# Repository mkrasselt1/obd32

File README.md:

# obd32
The goal of this project is to create a esp32 based pcb and software to
catch and submit automotive data from obd2 ports of supported vehicles 
to a given (list of ) endpoints(s). 

Anyone is free to join our goal to make the hardware reliable and affordable.

current plan conatins the featureset of:

    - esp32 based microprocessor
    - direct canbus via tranciever chip MCP2562-e
    - db9 for obd2 connection
    - wifi connection to hotsport or
    - onboard switchable usb port for lte-wifi-router 
    - ~~bluetooth connection compatible with elm327ds~~
    - micro sd card slot for configuration, logging and cache
    - ota updates via github releases
    - build in webfrontend
    - low power sleep mode (canbus activity and battery voltage)
    - gps for location and altitude sync
    - communication protocolls: https-post, websocket, mqtt

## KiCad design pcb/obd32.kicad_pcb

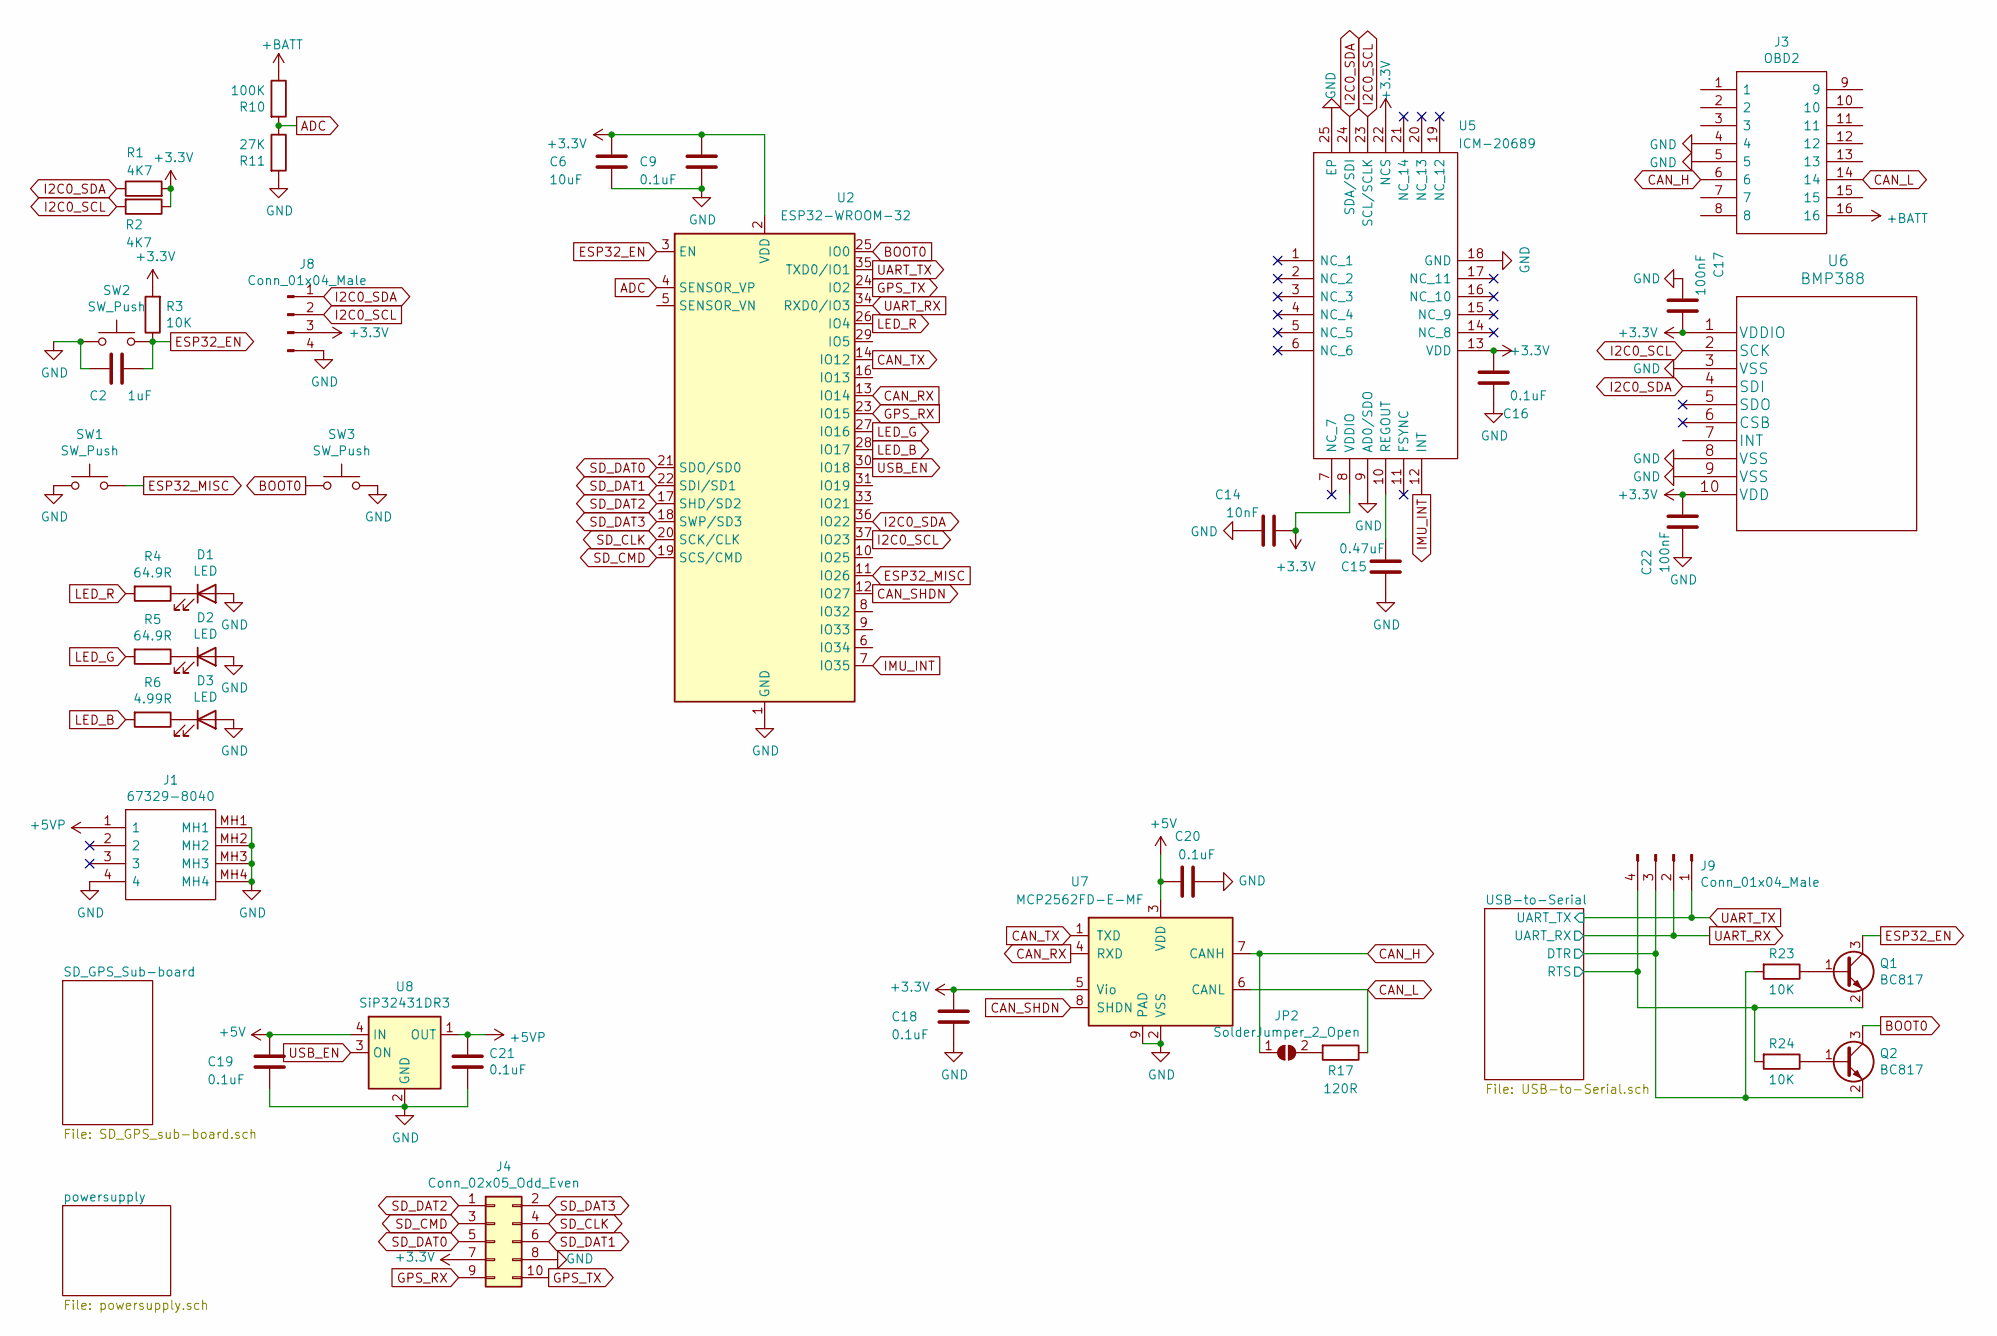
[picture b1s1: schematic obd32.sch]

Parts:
C2: 1uF; C_0402_1005Metric
C6: 10uF; C_0805_2012Metric
C9, C16, C18, C19, C20, C21: 0.1uF; C_0402_1005Metric
C14: 10nF; C_0402_1005Metric
C15: 0.47uF; C_0402_1005Metric
C17, C22: 100nF; C_0402_1005Metric
D1, D2, D3: LED; LED_0402_1005Metric
J1: 67329-8040; 673298040; Manufacturer_Part_Number 67329-8040; Mouser Part Number 538-67329-8040
J3: OBD2; Manufacturer_Part_Number OBD2
J4: Conn_02x05_Odd_Even; PinSocket_2x05_P2.54mm_Vertical
J8, J9: Conn_01x04_Male; PinHeader_1x04_P2.54mm_Vertical
JP2: SolderJumper_2_Open; SolderJumper-2_P1.3mm_Open_RoundedPad1.0x1.5mm
Q1, Q2: BC817; SOT-23
R1, R2: 4K7; R_0603_1608Metric
R3, R23, R24: 10K; R_0402_1005Metric
R4, R5: 64.9R; R_0402_1005Metric
R6: 4.99R; R_0402_1005Metric
R10: 100K; R_0402_1005Metric
R11: 27K; R_0402_1005Metric
R17: 120R; R_0402_1005Metric
SW1, SW2, SW3: SW_Push; SW_SPST_B3U-3000P-B
U2: ESP32-WROOM-32; ESP32-WROOM-32U
U5: ICM-20689; QFN50P400X400X95-25N-D; Manufacturer_Part_Number ICM-20689; Mouser Part Number 410-ICM-20689
U6: BMP388
U7: MCP2562FD-E-MF; DFN-8-1EP_3x3mm_P0.65mm_EP1.55x2.4mm
U8: SiP32431DR3; SOT-363_SC-70-6

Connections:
+3V3: C6.1, C9.1, C14.2, C16.2, C17.2, C18.2, C22.2, J4.7, J8.3, R1.2, R2.1, R3.2, U2.2 (VDD), U5.8 (VDDIO), U5.13 (VDD), U5.22 (NCS), U6.1 (VDDIO), U6.10 (VDD), U7.5 (Vio); also elsewhere on the board
+5V: C19.1, C20.1, U7.3 (VDD), U8.4 (IN); also elsewhere on the board
+5VP: C21.1, J1.1, U8.1 (OUT)
+BATT: J3.16, R10.1; also elsewhere on the board
/USB-to-Serial/DTR: J9.3, Q2.2 (E), R23.2; also elsewhere on the board
/USB-to-Serial/RTS: J9.4, Q1.2 (E), R24.2; also elsewhere on the board
ADC: R10.2, R11.1, U2.4 (SENSOR_VP)
BOOT0: Q2.3 (C), SW3.1, U2.25 (IO0)
CAN_H: J3.6, JP2.1 (A), U7.7 (CANH)
CAN_L: J3.14, R17.1, U7.6 (CANL)
CAN_RX: U2.13 (IO14), U7.4 (RXD)
CAN_SHDN: U2.12 (IO27), U7.8 (SHDN)
CAN_TX: U2.14 (IO12), U7.1 (TXD)
ESP32_EN: C2.2, Q1.3 (C), R3.1, SW2.2, U2.3 (EN)
ESP32_MISC: SW1.2, U2.11 (IO26)
GND: C2.1, C6.2, C9.2, C14.1, C15.1, C16.1, C17.1, C18.1, C19.2, C20.2, C21.2, C22.1, D1.2 (A), D2.2 (A), D3.2 (A), J1.4, J1.MH1, J1.MH2, J1.MH3, J1.MH4, J3.4, J3.5, J4.8, J8.4, R11.2, SW1.1, SW2.1, SW3.2, U2.1 (GND), U2.15 (GND), U2.38 (GND), U2.39 (GND), U5.9 (AD0/SDO), U5.18 (GND), U5.25 (EP), U6.3 (VSS), U6.8 (VSS), U6.9 (VSS), U7.2 (VSS), U7.9 (PAD), U8.2 (GND), U8.5 (GND); also elsewhere on the board
GPS_RX: J4.9, U2.23 (IO15)
GPS_TX: J4.10, U2.24 (IO2)
I2C0_SCL: J8.2, R2.2, U2.37 (IO23), U5.23 (SCL/SCLK), U6.2 (SCK)
I2C0_SDA: J8.1, R1.1, U2.36 (IO22), U5.24 (SDA/SDI), U6.4 (SDI)
IMU_INT: U2.7 (IO35), U5.12 (INT)
LED_B: R6.2, U2.28 (IO17)
LED_G: R5.2, U2.27 (IO16)
LED_R: R4.2, U2.26 (IO4)
unnamed: C15.2, U5.10 (REGOUT)
unnamed: D1.1 (K), R4.1
unnamed: D2.1 (K), R5.1
unnamed: D3.1 (K), R6.1
unnamed: JP2.2 (B), R17.2
unnamed: Q1.1 (B), R23.1
unnamed: Q2.1 (B), R24.1
SD_CLK: J4.4, U2.20 (SCK/CLK)
SD_CMD: J4.3, U2.19 (SCS/CMD)
SD_DAT0: J4.5, U2.21 (SDO/SD0)
SD_DAT1: J4.6, U2.22 (SDI/SD1)
SD_DAT2: J4.1, U2.17 (SHD/SD2)
SD_DAT3: J4.2, U2.18 (SWP/SD3)
UART_RX: J9.2, U2.34 (RXD0/IO3); also elsewhere on the board
UART_TX: J9.1, U2.35 (TXD0/IO1); also elsewhere on the board
USB_EN: U2.30 (IO18), U8.3 (ON)

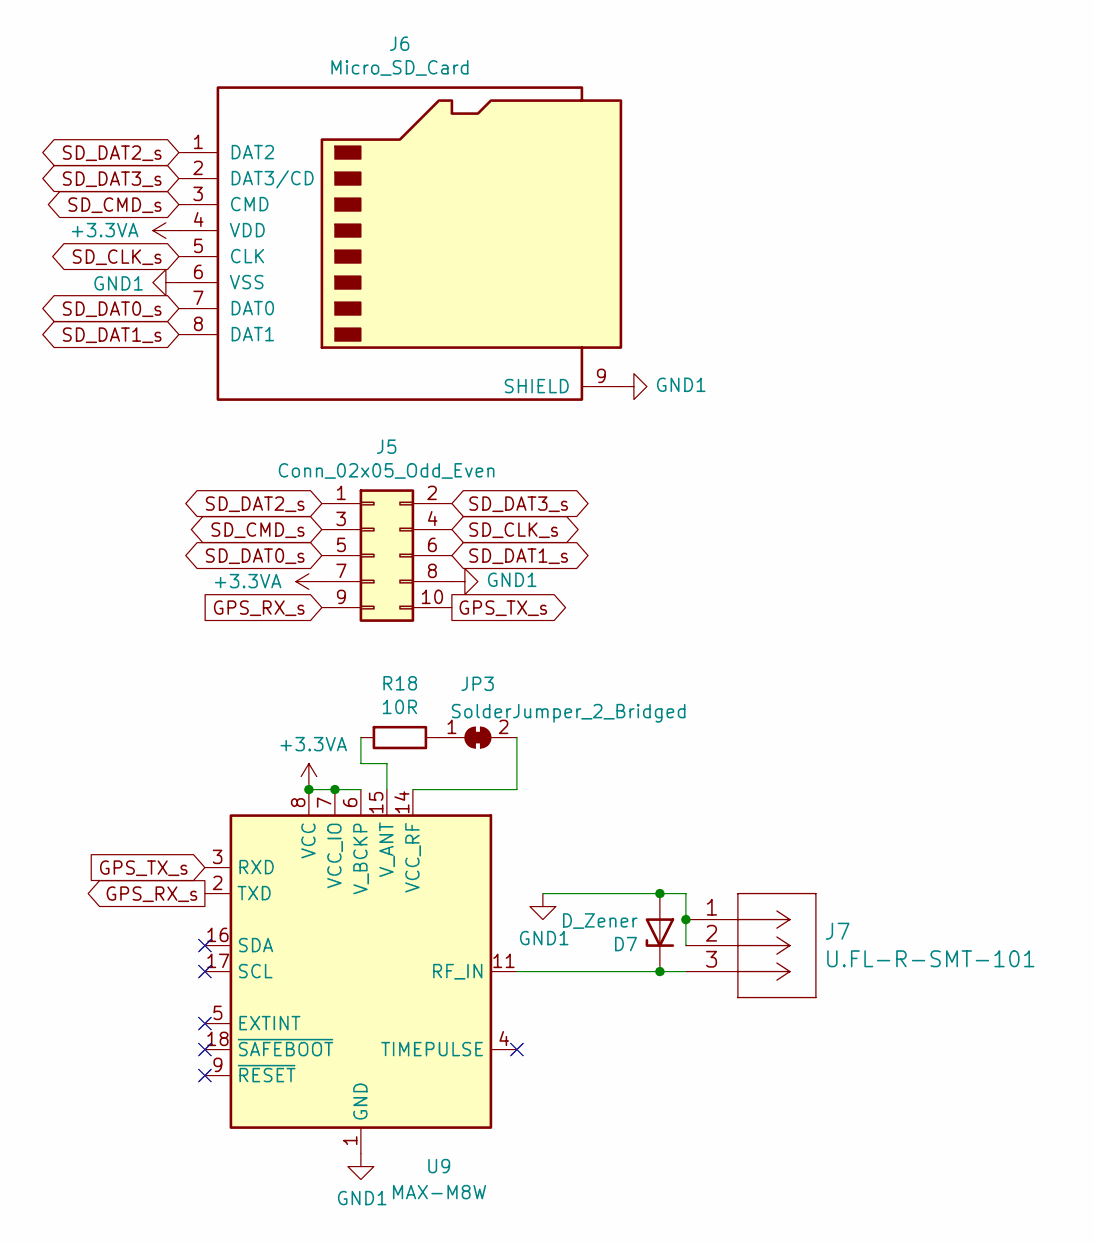
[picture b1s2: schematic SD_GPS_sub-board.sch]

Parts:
D7: D_Zener; D_0201_0603Metric
J5: Conn_02x05_Odd_Even; PinHeader_2x05_P2.54mm_Vertical
J6: Micro_SD_Card; microSD_HC_Hirose_DM3AT-SF-PEJM5
J7: U.FL-R-SMT-101
JP3: SolderJumper_2_Bridged; SolderJumper-2_P1.3mm_Bridged_RoundedPad1.0x1.5mm
R18: 10R; R_0402_1005Metric
U9: MAX-M8W; ublox_MAX

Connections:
+3.3VA: J5.7, J6.4 (VDD), U9.6 (V_BCKP), U9.7 (VCC_IO), U9.8 (VCC)
GND1: D7.2 (A), J5.8, J6.6 (VSS), J6.9 (SHIELD), J7.1 (GND), J7.2 (GND), U9.1 (GND), U9.10 (GND), U9.12 (GND)
GPS_RX_s: J5.9, U9.2 (TXD)
GPS_TX_s: J5.10, U9.3 (RXD)
unnamed: D7.1 (K), J7.3 (SIG), U9.11 (RF_IN)
unnamed: JP3.1 (A), R18.1
unnamed: JP3.2 (B), U9.14 (VCC_RF)
unnamed: R18.2, U9.15 (V_ANT)
SD_CLK_s: J5.4, J6.5 (CLK)
SD_CMD_s: J5.3, J6.3 (CMD)
SD_DAT0_s: J5.5, J6.7 (DAT0)
SD_DAT1_s: J5.6, J6.8 (DAT1)
SD_DAT2_s: J5.1, J6.1 (DAT2)
SD_DAT3_s: J5.2, J6.2 (DAT3/CD)

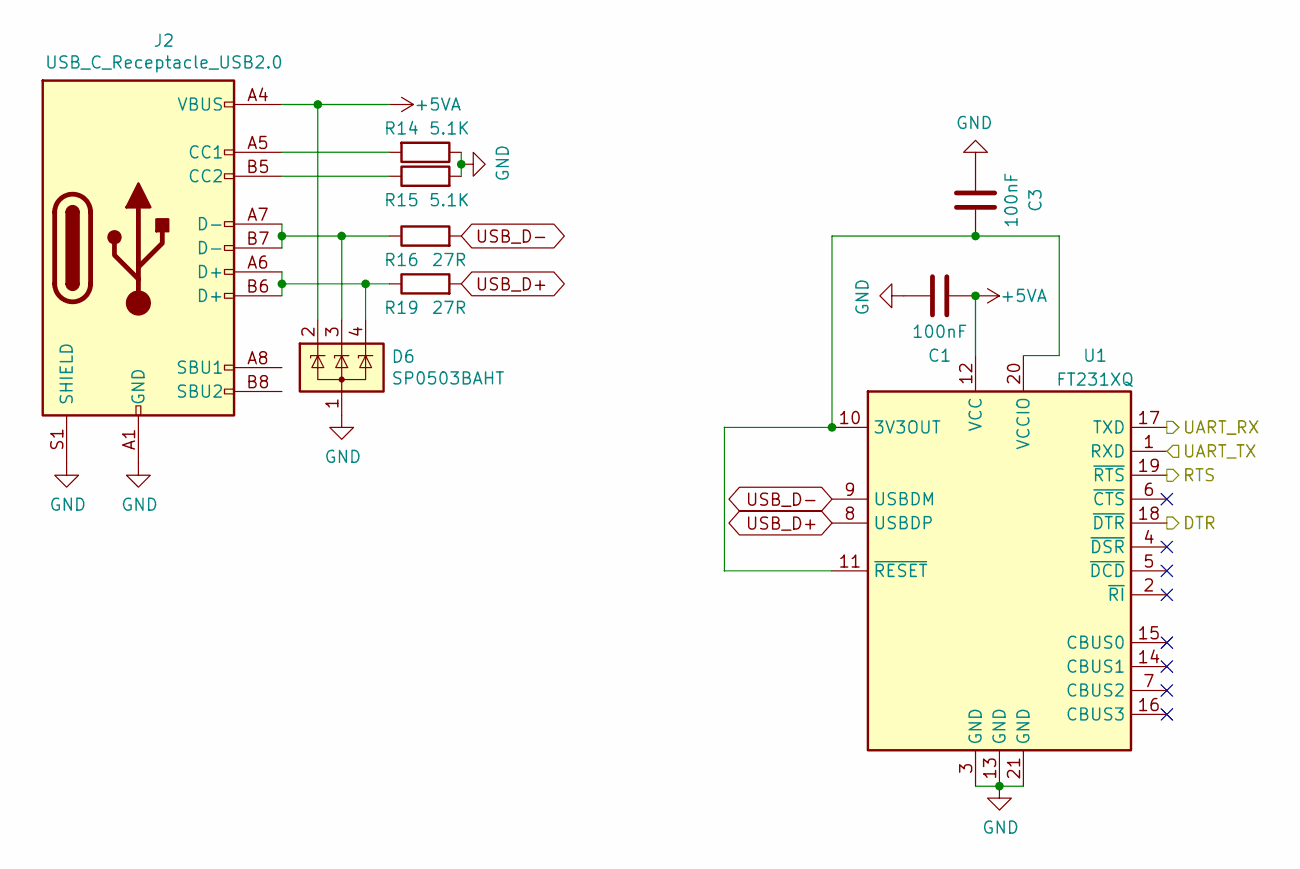
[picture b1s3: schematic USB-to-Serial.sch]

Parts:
C1, C3: 100nF; C_0805_2012Metric
D6: SP0503BAHT; SOT-143
J2: USB_C_Receptacle_USB2.0; USB_C_Receptacle_JAE_DX07S016JA1
R14, R15: 5.1K; R_0402_1005Metric
R16, R19: 27R; R_0402_1005Metric
U1: FT231XQ; QFN-20-1EP_4x4mm_P0.5mm_EP2.5x2.5mm

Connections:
+5VA: C1.2, D6.2 (K), J2.A4 (VBUS), J2.A9 (VBUS), J2.B4 (VBUS), J2.B9 (VBUS), U1.12 (VCC); also elsewhere on the board
/USB-to-Serial/DTR: U1.18 (~DTR); also elsewhere on the board
/USB-to-Serial/RTS: U1.19 (~RTS); also elsewhere on the board
GND: C1.1, C3.2, D6.1 (A), J2.A1 (GND), J2.A12 (GND), J2.B1 (GND), J2.B12 (GND), J2.S1 (SHIELD), R14.1, R15.2, U1.3 (GND), U1.13 (GND), U1.21 (GND); also elsewhere on the board
unnamed: C3.1, U1.10 (3V3OUT), U1.11 (~RESET), U1.20 (VCCIO)
unnamed: D6.3 (K), J2.A7 (D-), J2.B7 (D-), R16.1
unnamed: D6.4 (K), J2.A6 (D+), J2.B6 (D+), R19.1
unnamed: J2.A5 (CC1), R14.2
unnamed: J2.B5 (CC2), R15.1
UART_RX: U1.17 (TXD); also elsewhere on the board
UART_TX: U1.1 (RXD); also elsewhere on the board
USB_D+: R19.2, U1.8 (USBDP)
USB_D-: R16.2, U1.9 (USBDM)

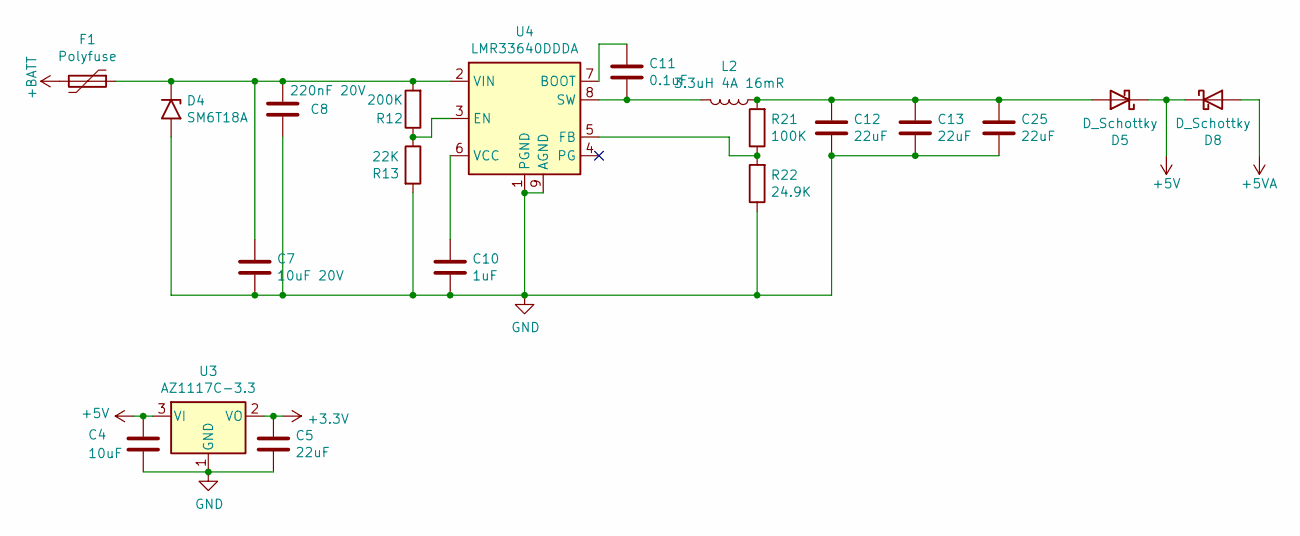
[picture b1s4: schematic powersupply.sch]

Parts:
C4: 10uF; C_0805_2012Metric
C5, C12, C13, C25: 22uF; C_0805_2012Metric
C7: 10uF 20V; C_0805_2012Metric
C8: 220nF 20V; C_0402_1005Metric
C10: 1uF; C_0402_1005Metric
C11: 0.1uF; C_0402_1005Metric
D4: SM6T18A; D_SMB
D5, D8: D_Schottky; D_SMA
F1: Polyfuse; Fuse_1812_4532Metric_Castellated
L2: 3.3uH 4A 16mR; TDK_SPM5030
R12: 200K; R_0402_1005Metric
R13: 22K; R_0402_1005Metric
R21: 100K; R_0402_1005Metric
R22: 24.9K; R_0402_1005Metric
U3: AZ1117C-3.3; SOT-89-3
U4: LMR33640DDDA; Texas_HSOP-8-1EP_3.9x4.9mm_P1.27mm_ThermalVias

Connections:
+3V3: C5.1, U3.2 (VO); also elsewhere on the board
+5V: C4.1, D5.1 (K), D8.1 (K), U3.3 (VI); also elsewhere on the board
+5VA: D8.2 (A); also elsewhere on the board
+BATT: F1.2; also elsewhere on the board
GND: C4.2, C5.2, C7.2, C8.2, C10.2, C12.2, C13.2, C25.2, D4.2 (A2), R13.2, R22.1, U3.1 (GND), U4.1 (PGND), U4.9 (AGND); also elsewhere on the board
unnamed: C7.1, C8.1, D4.1 (A1), F1.1, R12.2, U4.2 (VIN)
unnamed: C10.1, U4.6 (VCC)
unnamed: C11.1, U4.7 (BOOT)
unnamed: C11.2, L2.2, U4.8 (SW)
unnamed: C12.1, C13.1, C25.1, D5.2 (A), L2.1, R21.2
unnamed: R12.1, R13.1, U4.3 (EN)
unnamed: R21.1, R22.2, U4.5 (FB)

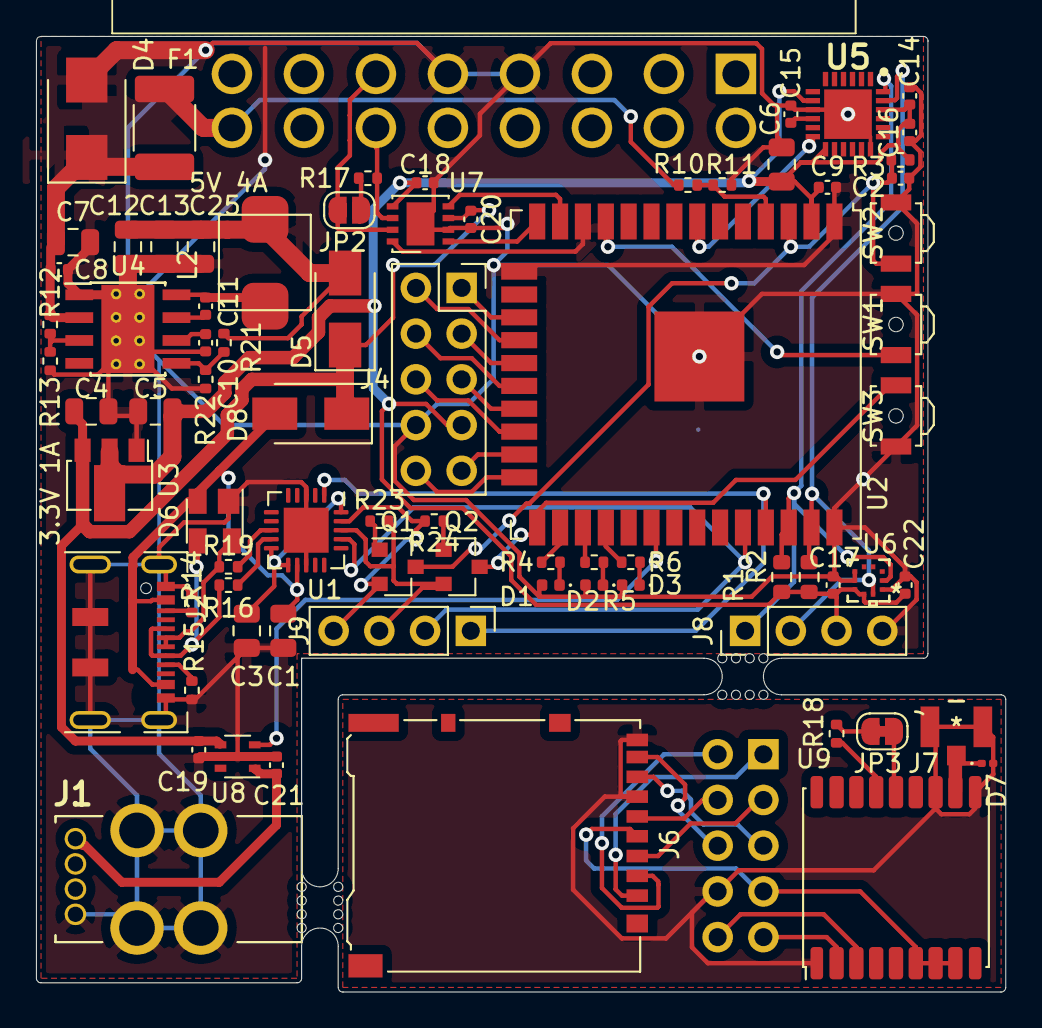
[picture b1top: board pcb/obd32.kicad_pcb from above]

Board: 2 copper layers, 53.8 x 53.1 mm, 78 parts (1 on the bottom side), 69 nets.

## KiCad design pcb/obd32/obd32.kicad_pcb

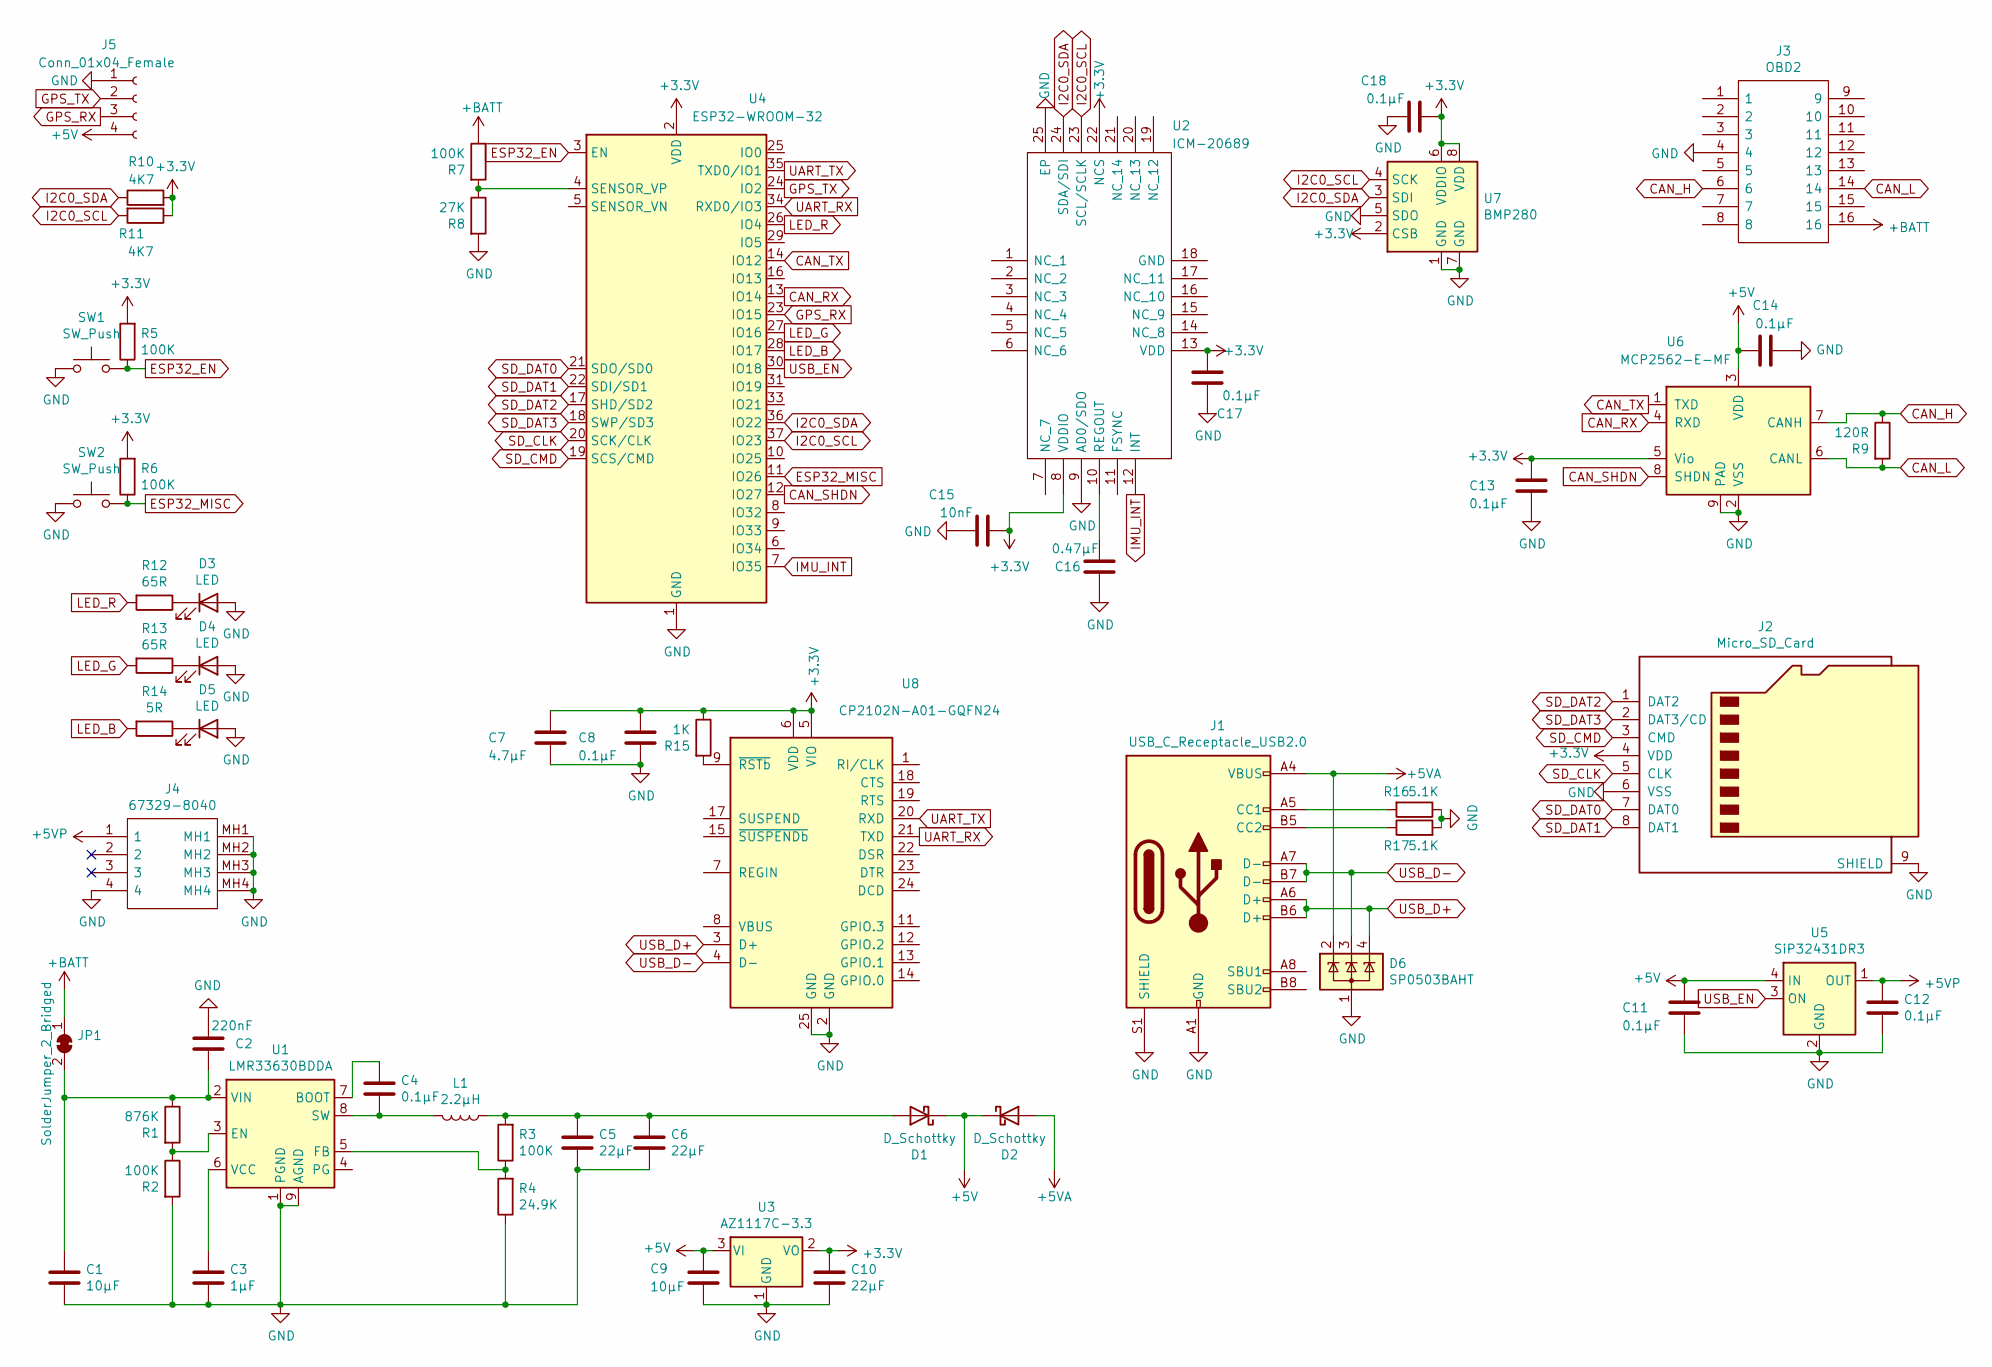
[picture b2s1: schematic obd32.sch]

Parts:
C1, C9: 10µF; C_0805_2012Metric
C2: 220nF; C_0805_2012Metric
C3: 1µF; C_0402_1005Metric
C4: 0.1µF; C_0402_1005Metric
C5, C6, C10: 22µF; C_0805_2012Metric
C7: 4.7µF; C_0201_0603Metric
C8, C11, C12, C13, C14, C17, C18: 0.1µF; C_0201_0603Metric
C15: 10nF; C_0201_0603Metric
C16: 0.47µF; C_0201_0603Metric
D1, D2: D_Schottky; D_SMA
D3, D4, D5: LED; LED_0402_1005Metric
D6: SP0503BAHT; SOT-143
J1: USB_C_Receptacle_USB2.0; USB_C_Receptacle_HRO_TYPE-C-31-M-12
J2: Micro_SD_Card; microSD_HC_Hirose_DM3AT-SF-PEJM5
J3: OBD2; Manufacturer_Part_Number OBD2
J4: 67329-8040; 673298040; Manufacturer_Part_Number 67329-8040; Mouser Part Number 538-67329-8040
J5: Conn_01x04_Female; PinSocket_1x04_P2.54mm_Vertical_SMD_Pin1Left
JP1: SolderJumper_2_Bridged; SolderJumper-2_P1.3mm_Bridged_RoundedPad1.0x1.5mm
L1: 2.2µH; TDK_SPM5030
R1: 876K; R_0201_0603Metric
R2, R3, R5, R6, R7: 100K; R_0201_0603Metric
R4: 24.9K; R_0201_0603Metric
R8: 27K; R_0201_0603Metric
R9: 120R; R_0201_0603Metric
R10, R11: 4K7; R_0201_0603Metric
R12, R13: 65R; R_0201_0603Metric
R14: 5R; R_0201_0603Metric
R15: 1K; R_0201_0603Metric
R16, R17: 5.1K; R_0201_0603Metric
SW1, SW2: SW_Push; SW_SPST_B3U-3000P-B
U1: LMR33630BDDA; Texas_HSOP-8-1EP_3.9x4.9mm_P1.27mm_ThermalVias
U2: ICM-20689; QFN50P400X400X95-25N-D; Manufacturer_Part_Number ICM-20689; Mouser Part Number 410-ICM-20689
U3: AZ1117C-3.3; SOT-89-3
U4: ESP32-WROOM-32
U5: SiP32431DR3; SOT-363_SC-70-6
U6: MCP2562-E-MF; DFN-8-1EP_3x3mm_P0.65mm_EP1.55x2.4mm
U7: BMP280; Bosch_LGA-8_2x2.5mm_P0.65mm_ClockwisePinNumbering
U8: CP2102N-A01-GQFN24; QFN-24-1EP_4x4mm_P0.5mm_EP2.6x2.6mm

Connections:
+3V3: C7.1, C8.1, C10.1, C13.2, C15.2, C17.2, C18.2, J2.4 (VDD), R5.2, R6.2, R10.2, R11.1, R15.1, U2.8 (VDDIO), U2.13 (VDD), U2.22 (NCS), U3.2 (VO), U4.2 (VDD), U6.5 (Vio), U7.2 (CSB), U7.6 (VDDIO), U7.8 (VDD), U8.5 (VIO), U8.6 (VDD)
+5V: C9.1, C11.1, C14.1, D1.1 (K), D2.1 (K), J5.4, U3.3 (VI), U5.4 (IN), U6.3 (VDD)
+5VA: D2.2 (A), D6.2 (K), J1.A4 (VBUS), J1.A9 (VBUS), J1.B4 (VBUS), J1.B9 (VBUS)
+5VP: C12.1, J4.1, U5.1 (OUT)
+BATT: J3.16, JP1.1 (A), R7.1
CAN_H: J3.6, R9.1, U6.7 (CANH)
CAN_L: J3.14, R9.2, U6.6 (CANL)
CAN_RX: U4.13 (IO14), U6.4 (RXD)
CAN_SHDN: U4.12 (IO27), U6.8 (SHDN)
CAN_TX: U4.14 (IO12), U6.1 (TXD)
ESP32_EN: R5.1, SW1.2, U4.3 (EN)
ESP32_MISC: R6.1, SW2.2, U4.11 (IO26)
GND: C1.2, C2.1, C3.2, C5.2, C6.2, C7.2, C8.2, C9.2, C10.2, C11.2, C12.2, C13.1, C14.2, C15.1, C16.1, C17.1, C18.1, D3.2 (A), D4.2 (A), D5.2 (A), D6.1 (A), J1.A1 (GND), J1.A12 (GND), J1.B1 (GND), J1.B12 (GND), J1.S1 (SHIELD), J2.6 (VSS), J2.9 (SHIELD), J3.4, J4.4, J4.MH1, J4.MH2, J4.MH3, J4.MH4, J5.1, R2.2, R4.1, R8.2, R16.1, R17.2, SW1.1, SW2.1, U1.1 (PGND), U1.9 (AGND), U2.9 (AD0/SDO), U2.25 (EP), U3.1 (GND), U4.1 (GND), U4.15 (GND), U4.38 (GND), U4.39 (GND), U5.2 (GND), U5.5 (GND), U6.2 (VSS), U6.9 (PAD), U7.1 (GND), U7.5 (SDO), U7.7 (GND), U8.2 (GND), U8.25 (GND)
GPS_RX: J5.3, U4.23 (IO15)
GPS_TX: J5.2, U4.24 (IO2)
I2C0_SCL: R11.2, U2.23 (SCL/SCLK), U4.37 (IO23), U7.4 (SCK)
I2C0_SDA: R10.1, U2.24 (SDA/SDI), U4.36 (IO22), U7.3 (SDI)
IMU_INT: U2.12 (INT), U4.7 (IO35)
LED_B: R14.2, U4.28 (IO17)
LED_G: R13.2, U4.27 (IO16)
LED_R: R12.2, U4.26 (IO4)
unnamed: C1.1, C2.2, JP1.2 (B), R1.1, U1.2 (VIN)
unnamed: C3.1, U1.6 (VCC)
unnamed: C4.1, U1.7 (BOOT)
unnamed: C4.2, L1.2, U1.8 (SW)
unnamed: C5.1, C6.1, D1.2 (A), L1.1, R3.2
unnamed: C16.2, U2.10 (REGOUT)
unnamed: D3.1 (K), R12.1
unnamed: D4.1 (K), R13.1
unnamed: D5.1 (K), R14.1
unnamed: J1.A5 (CC1), R16.2
unnamed: J1.B5 (CC2), R17.1
unnamed: R1.2, R2.1, U1.3 (EN)
unnamed: R3.1, R4.2, U1.5 (FB)
unnamed: R7.2, R8.1, U4.4 (SENSOR_VP)
unnamed: R15.2, U8.9 (~RSTb)
SD_CLK: J2.5 (CLK), U4.20 (SCK/CLK)
SD_CMD: J2.3 (CMD), U4.19 (SCS/CMD)
SD_DAT0: J2.7 (DAT0), U4.21 (SDO/SD0)
SD_DAT1: J2.8 (DAT1), U4.22 (SDI/SD1)
SD_DAT2: J2.1 (DAT2), U4.17 (SHD/SD2)
SD_DAT3: J2.2 (DAT3/CD), U4.18 (SWP/SD3)
UART_RX: U4.34 (RXD0/IO3), U8.21 (TXD)
UART_TX: U4.35 (TXD0/IO1), U8.20 (RXD)
USB_D+: D6.4 (K), J1.A6 (D+), J1.B6 (D+), U8.3 (D+)
USB_D-: D6.3 (K), J1.A7 (D-), J1.B7 (D-), U8.4 (D-)
USB_EN: U4.30 (IO18), U5.3 (ON)

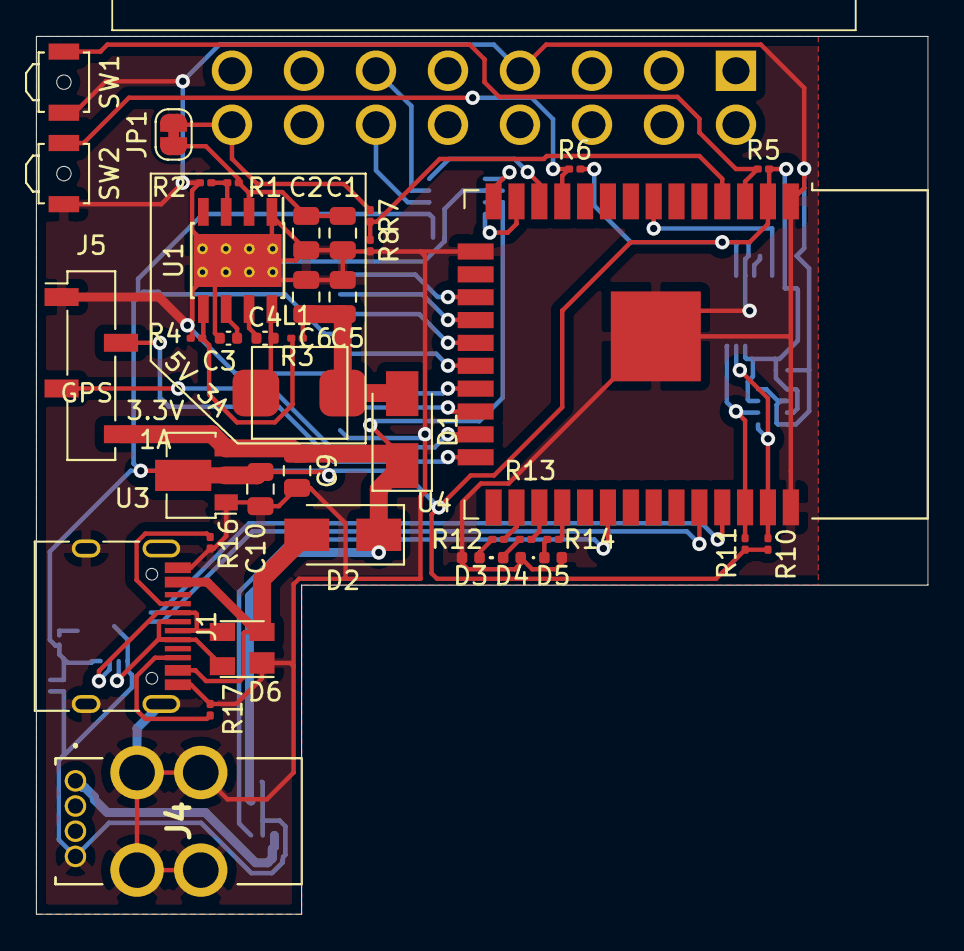
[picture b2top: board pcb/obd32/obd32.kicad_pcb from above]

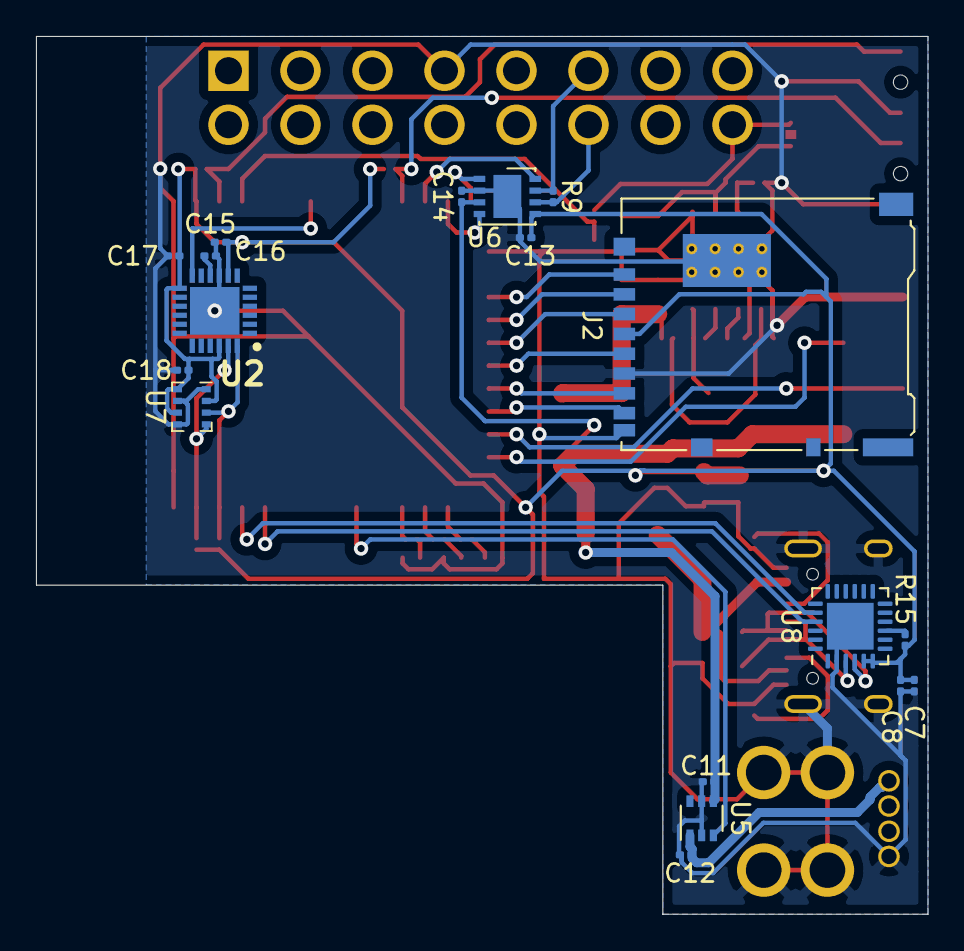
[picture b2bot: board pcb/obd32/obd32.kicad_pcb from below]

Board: 2 copper layers, 49.5 x 48.8 mm, 58 parts (18 on the bottom side), 47 nets.

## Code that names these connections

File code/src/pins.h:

// vv GPIO number vv
#define GPIO_UART_RX 3		// UART0
#define GPIO_UART_TX 1		// UART0
#define GPIO_GPS_RX 15		// UART2
#define GPIO_GPS_TX 2		// UART2
#define GPIO_CAN_RX 14		// CAN
#define GPIO_CAN_TX 12		// CAN
#define GPIO_I2C0_SDA 22	// I2C
#define GPIO_I2C0_SCL 23	// I2C
#define GPIO_ADC 36 		// ADC1_CH0
#define GPIO_BTN1 26		// ESP32_MISC
#define GPIO_USB_EN 18
#define GPIO_LED_R 4
#define GPIO_LED_G 16
#define GPIO_LED_B 17
#define GPIO_CS_SDCARD 4    // Chip Select SD Card

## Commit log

2020-11-02 Add: Readme Project Description \n Add: Basic PCB Design
2020-11-02 Fix: readme markdown correction
2020-11-02 Add: basic pio project
2020-11-09 FIX: Simple ODB2 Scanner
2020-11-09 Add: Simple MQTT Client
2020-11-13 adjust pio to my platform
2020-11-14 first prototype of decoder
2020-11-28 working prototype of ISO-TP- and car decoder
2020-11-29 1st draft
2020-11-30 Maybe version of board
2020-12-02 Board: Add USB-C and CP2102 UART converter
2020-12-02 Board: Add cuttable solder jumper to allow disconnection from 12V rail
2020-12-03 Board: replace pressure sensor with more common bmp280
2020-12-07 Add header for pin mapping; put stuff into main
2020-12-07 Board: some refinement; Add button BOOT0
2020-12-27 PIO: use hopefulle fitting board
2020-12-27 OBD: Work towards generic decoder
2021-02-21 Add: Base Code Send SOC to EVNotify
2021-02-21 Fix: Revert car_decode out of obd file, merge mistake
2021-02-21 PCB: Move components from bottom to top side of board. Move SD-card slot to sub board. Add SAM-M8N GPS-receiver
2021-02-22 Add: Extended and Location Sync Messages to EvNotify Sender
2021-02-25 BMP280 was replaced with BMP388, adjust code accordingly
2021-02-26 Add: Seperate Threads for GPS and Backend
2021-03-07 Board: use different USB-C Receptable
2021-03-07 Board: add Gerber files
2021-06-03 Board: Adjustments
2021-11-10 Update README.md
    Fixed markdown of readme
2022-01-23 Moved prototype code to main.old; Add: OTA Update Capabilitys; Add: WEB Interface with events and websocket server Add: OTA Web Interface
2026-04-27 ci: auto-mirror to GitLab

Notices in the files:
parts and their libraries:
Copyright 2016 Accelerated Designs. All rights reserved.
